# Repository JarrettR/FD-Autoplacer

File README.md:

# Force Directed Autoplacer

Physics-defined circuit board layout.

## The Theory

From Wikipedia:

> Force-directed graph drawing algorithms are a class of algorithms for drawing graphs in an aesthetically-pleasing way. Their purpose is to position the nodes of a graph in two-dimensional or three-dimensional space so that all the edges are of more or less equal length and there are as few crossing edges as possible, by assigning forces among the set of edges and the set of nodes, based on their relative positions, and then using these forces either to simulate the motion of the edges and nodes or to minimize their energy.

Oh my. That sounds like what my brain is doing while I'm laying out a circuit board.

## Why?

The idea has been bouncing around in my head for a few months. I also have a thing for making perfectly valid, competent PCBs that make other engineers uncomfortable in ways they can't articulate or defend.

## Usage

- Run `python main.py` to start an example PCB
- Deselect nets as desired. Usually power and ground nets are too dense to be useful
- Play around with attractor and repulsor forces
- To load in a different PCB, edit line 14 of `pcbparse.py`
- Change the zoom of the main window in line 17 of `main.py`. Pan is not implemented.

## Future Work

- Clean up the hacks that require editing the code for each project: Better file input, automatic zoom and pan
- Respect the board outline layer, so components can bounce around inside it
- Turn this into a KiCad module so that it can be launched from within
- Exporting footprint positions back into a PCB file. Rewriting the PCB file is one strategy, but the KiCad API is straightforward, too
- Fix the many edge cases that break the project
- Make a PCB with zero footprints that have right angles
- Come up with more fun examples and animations - Please submit them in Issues!

## Likelihood of Most of That Actually Happening

Low. This repo can be seen as an experiment that has served its purpose.

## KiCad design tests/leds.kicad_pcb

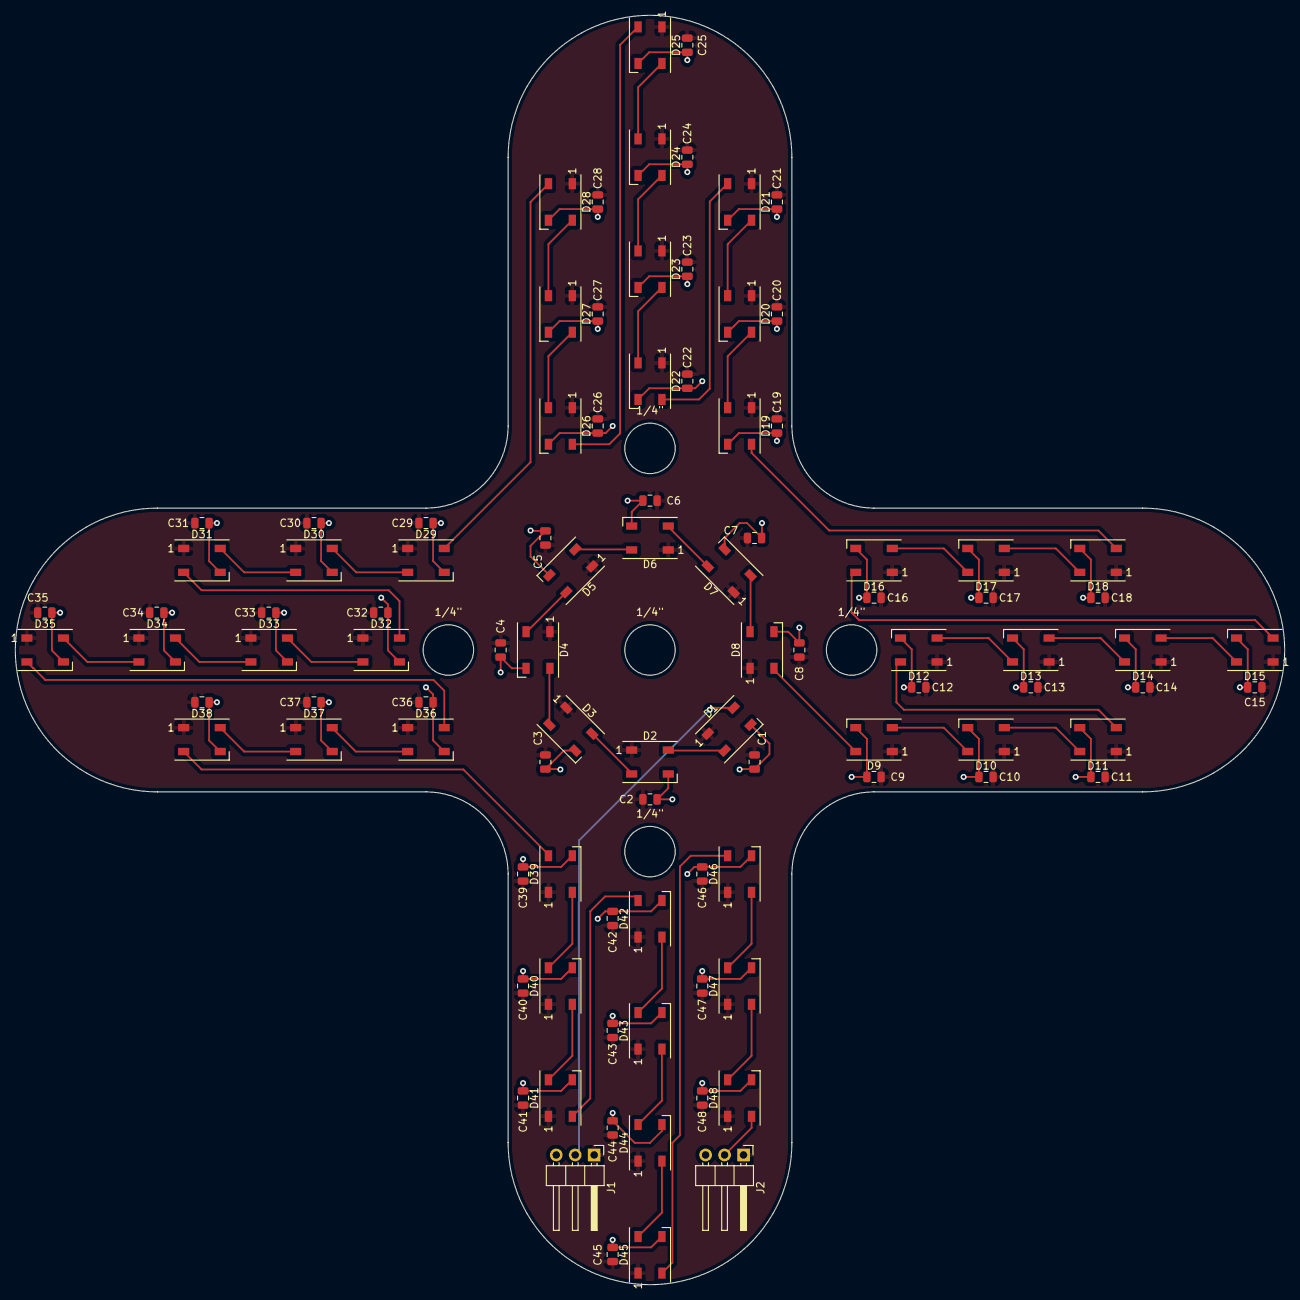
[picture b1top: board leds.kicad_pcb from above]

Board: 2 copper layers, 170.0 x 170.0 mm, 103 parts (0 on the bottom side), 51 nets.

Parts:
1/4", 1/4"#2, 1/4"#3, 1/4"#4, 1/4"#5: MountingHole 0.25 - 20
C1, C2, C3, C4, C5, C6, C7, C8, C9, C10, C11, C12, C13, C14, C15, C16, C17, C18, C19, C20, C21, C22, C23, C24, C25, C26, C27, C28, C29, C30, C31, C32, C33, C34, C35, C36, C37, C38, C39, C40, C41, C42, C43, C44, C45, C46, C47, C48: 0.1 uF; C_0805_2012Metric silk moved
D1, D2, D3, D4, D5, D6, D7, D8, D9, D10, D11, D12, D13, D14, D15, D16, D17, D18, D19, D20, D21, D22, D23, D24, D25, D26, D27, D28, D29, D30, D31, D32, D33, D34, D35, D36, D37, D38, D39, D40, D41, D42, D43, D44, D45, D46, D47, D48: WS2812B; LED_WS2812B_PLCC4_5.0x5.0mm_P3.2mm
J1, J2: Conn_01x03; PinHeader_1x03_P2.54mm_Horizontal

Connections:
+5V: C1.2, C2.2, C3.2, C4.2, C5.2, C6.2, C7.2, C8.2, C9.2, C10.2, C11.2, C12.2, C13.2, C14.2, C15.2, C16.2, C17.2, C18.2, C19.2, C20.2, C21.2, C22.2, C23.2, C24.2, C25.2, C26.2, C27.2, C28.2, C29.2, C30.2, C31.2, C32.2, C33.2, C34.2, C35.2, C36.2, C37.2, C38.2, C39.2, C40.2, C41.2, C42.2, C43.2, C44.2, C45.2, C46.2, C47.2, C48.2, D1.1 (VDD), D2.1 (VDD), D3.1 (VDD), D4.1 (VDD), D5.1 (VDD), D6.1 (VDD), D7.1 (VDD), D8.1 (VDD), D9.1 (VDD), D10.1 (VDD), D11.1 (VDD), D12.1 (VDD), D13.1 (VDD), D14.1 (VDD), D15.1 (VDD), D16.1 (VDD), D17.1 (VDD), D18.1 (VDD), D19.1 (VDD), D20.1 (VDD), D21.1 (VDD), D22.1 (VDD), D23.1 (VDD), D24.1 (VDD), D25.1 (VDD), D26.1 (VDD), D27.1 (VDD), D28.1 (VDD), D29.1 (VDD), D30.1 (VDD), D31.1 (VDD), D32.1 (VDD), D33.1 (VDD), D34.1 (VDD), D35.1 (VDD), D36.1 (VDD), D37.1 (VDD), D38.1 (VDD), D39.1 (VDD), D40.1 (VDD), D41.1 (VDD), D42.1 (VDD), D43.1 (VDD), D44.1 (VDD), D45.1 (VDD), D46.1 (VDD), D47.1 (VDD), D48.1 (VDD), J1.1, J2.1
/23 LEDs1/DIN: D25.2 (DOUT), D26.4 (DIN)
/23 LEDs1/DOUT: D48.2 (DOUT), J2.2
/25 LEDs/DIN: D1.4 (DIN), J1.2
GND: C1.1, C2.1, C3.1, C4.1, C5.1, C6.1, C7.1, C8.1, C9.1, C10.1, C11.1, C12.1, C13.1, C14.1, C15.1, C16.1, C17.1, C18.1, C19.1, C20.1, C21.1, C22.1, C23.1, C24.1, C25.1, C26.1, C27.1, C28.1, C29.1, C30.1, C31.1, C32.1, C33.1, C34.1, C35.1, C36.1, C37.1, C38.1, C39.1, C40.1, C41.1, C42.1, C43.1, C44.1, C45.1, C46.1, C47.1, C48.1, D1.3 (VSS), D2.3 (VSS), D3.3 (VSS), D4.3 (VSS), D5.3 (VSS), D6.3 (VSS), D7.3 (VSS), D8.3 (VSS), D9.3 (VSS), D10.3 (VSS), D11.3 (VSS), D12.3 (VSS), D13.3 (VSS), D14.3 (VSS), D15.3 (VSS), D16.3 (VSS), D17.3 (VSS), D18.3 (VSS), D19.3 (VSS), D20.3 (VSS), D21.3 (VSS), D22.3 (VSS), D23.3 (VSS), D24.3 (VSS), D25.3 (VSS), D26.3 (VSS), D27.3 (VSS), D28.3 (VSS), D29.3 (VSS), D30.3 (VSS), D31.3 (VSS), D32.3 (VSS), D33.3 (VSS), D34.3 (VSS), D35.3 (VSS), D36.3 (VSS), D37.3 (VSS), D38.3 (VSS), D39.3 (VSS), D40.3 (VSS), D41.3 (VSS), D42.3 (VSS), D43.3 (VSS), D44.3 (VSS), D45.3 (VSS), D46.3 (VSS), D47.3 (VSS), D48.3 (VSS), J1.3, J2.3
unnamed: D1.2 (DOUT), D2.4 (DIN)
unnamed: D2.2 (DOUT), D3.4 (DIN)
unnamed: D3.2 (DOUT), D4.4 (DIN)
unnamed: D4.2 (DOUT), D5.4 (DIN)
unnamed: D5.2 (DOUT), D6.4 (DIN)
unnamed: D6.2 (DOUT), D7.4 (DIN)
unnamed: D7.2 (DOUT), D8.4 (DIN)
unnamed: D8.2 (DOUT), D9.4 (DIN)
unnamed: D10.2 (DOUT), D11.4 (DIN)
unnamed: D9.2 (DOUT), D10.4 (DIN)
unnamed: D11.2 (DOUT), D12.4 (DIN)
unnamed: D12.2 (DOUT), D13.4 (DIN)
unnamed: D13.2 (DOUT), D14.4 (DIN)
unnamed: D14.2 (DOUT), D15.4 (DIN)
unnamed: D15.2 (DOUT), D16.4 (DIN)
unnamed: D16.2 (DOUT), D17.4 (DIN)
unnamed: D17.2 (DOUT), D18.4 (DIN)
unnamed: D18.2 (DOUT), D19.4 (DIN)
unnamed: D19.2 (DOUT), D20.4 (DIN)
unnamed: D20.2 (DOUT), D21.4 (DIN)
unnamed: D21.2 (DOUT), D22.4 (DIN)
unnamed: D22.2 (DOUT), D23.4 (DIN)
unnamed: D23.2 (DOUT), D24.4 (DIN)
unnamed: D24.2 (DOUT), D25.4 (DIN)
unnamed: D26.2 (DOUT), D27.4 (DIN)
unnamed: D27.2 (DOUT), D28.4 (DIN)
unnamed: D28.2 (DOUT), D29.4 (DIN)
unnamed: D29.2 (DOUT), D30.4 (DIN)
unnamed: D30.2 (DOUT), D31.4 (DIN)
unnamed: D31.2 (DOUT), D32.4 (DIN)
unnamed: D32.2 (DOUT), D33.4 (DIN)
unnamed: D33.2 (DOUT), D34.4 (DIN)
unnamed: D34.2 (DOUT), D35.4 (DIN)
unnamed: D35.2 (DOUT), D36.4 (DIN)
unnamed: D36.2 (DOUT), D37.4 (DIN)
unnamed: D37.2 (DOUT), D38.4 (DIN)
unnamed: D38.2 (DOUT), D39.4 (DIN)
unnamed: D39.2 (DOUT), D40.4 (DIN)
unnamed: D40.2 (DOUT), D41.4 (DIN)
unnamed: D41.2 (DOUT), D42.4 (DIN)
unnamed: D42.2 (DOUT), D43.4 (DIN)
unnamed: D43.2 (DOUT), D44.4 (DIN)
unnamed: D44.2 (DOUT), D45.4 (DIN)
unnamed: D45.2 (DOUT), D46.4 (DIN)
unnamed: D46.2 (DOUT), D47.4 (DIN)
unnamed: D47.2 (DOUT), D48.4 (DIN)

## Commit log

2023-02-14 Initial tkinter window
2023-02-14 Layout tweaking
2023-02-14 Made OOP
2023-02-15 Reading out PCB nets
2023-02-16 Got option box displaying nets
2023-02-16 Displaying module courtyard with position
2023-02-16 Added module pads
2023-02-17 Net association with footprints
2023-02-20 Slightly better net handling
2023-02-21 Nets are drawn
2023-02-21 Footprints moving with nets regenerating\\\\\\\\\'
2023-02-21 Bouncing without damping
2023-02-21 Damping and split up attraction / repulsion
2023-02-22 Rotation works... poorly. Time for a refactor
2023-02-22 Refactor, drawing currently broken
2023-02-23 Drawing fixed
2023-02-23 Animation fixed
2023-02-23 Calculation fixed
2023-02-23 Rotation fixed
2023-02-23 Torque implemented
2023-02-23 Reset working
2023-02-23 Simulation params available from UI
2023-02-23 Fixed reset
2023-02-23 Disablng nets implemented
2023-02-24 Fixed complex edge cases
2023-02-28 Rough scrollbar working
2023-02-28 Interface creation cleaanup
2023-03-01 Massive performance boost
2023-03-01 better framerate calcs
2023-03-01 Obeys footprint locked property
2023-03-01 Colours switched over to black BG
2023-03-01 Identified through-hples
2023-03-01 Rotation initially broken
2023-03-03 Fixed anchor rotation
2023-03-03 Updated window title
2023-03-03 Updated docs
2023-03-03 Filename corrected for the input PCB
2023-03-03 Clarifying current state
2024-03-27 Added pymunk example
2024-03-28 FP courtyards implemented
2024-03-28 Running with imported footprint courtyards
2024-03-28 Zoom and scale for this particular board
2024-03-28 Fiddling with COG
2024-04-01 Fixed moment of inertia, gravity, and mass
2024-04-02 Pads added and damped spring tested
2024-04-04 Nets working
2024-04-04 Tweaked values and removed damping spring visuals
2024-04-05 Locked footprints now added as static bodies
2024-04-05 Okay fine, recursion is required
2024-12-07 Added Arc edge.cuts as simplified line outlines
2024-12-07 Added sample pyvenv.cfg to run with PCBNew-enabled Python
